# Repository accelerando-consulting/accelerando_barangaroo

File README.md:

# Accelerando Barangaroo

This is a simple breakout board for the eByte E73 module with nrf52832
microcontroller.  This board requires minimal parts, in fact it can
work with only the module and no other parts.

Add buttons and LEDs if you need, and there is space for two QWIIC
(I2C) sockets.

The board can be used with Arduino (Sandeep Mistry's nrf port with the
generic nrf52 target), or with Micro Python or Zephyr OS using the
included board definitions.

The circuit board files (for KiCad 5) are included.

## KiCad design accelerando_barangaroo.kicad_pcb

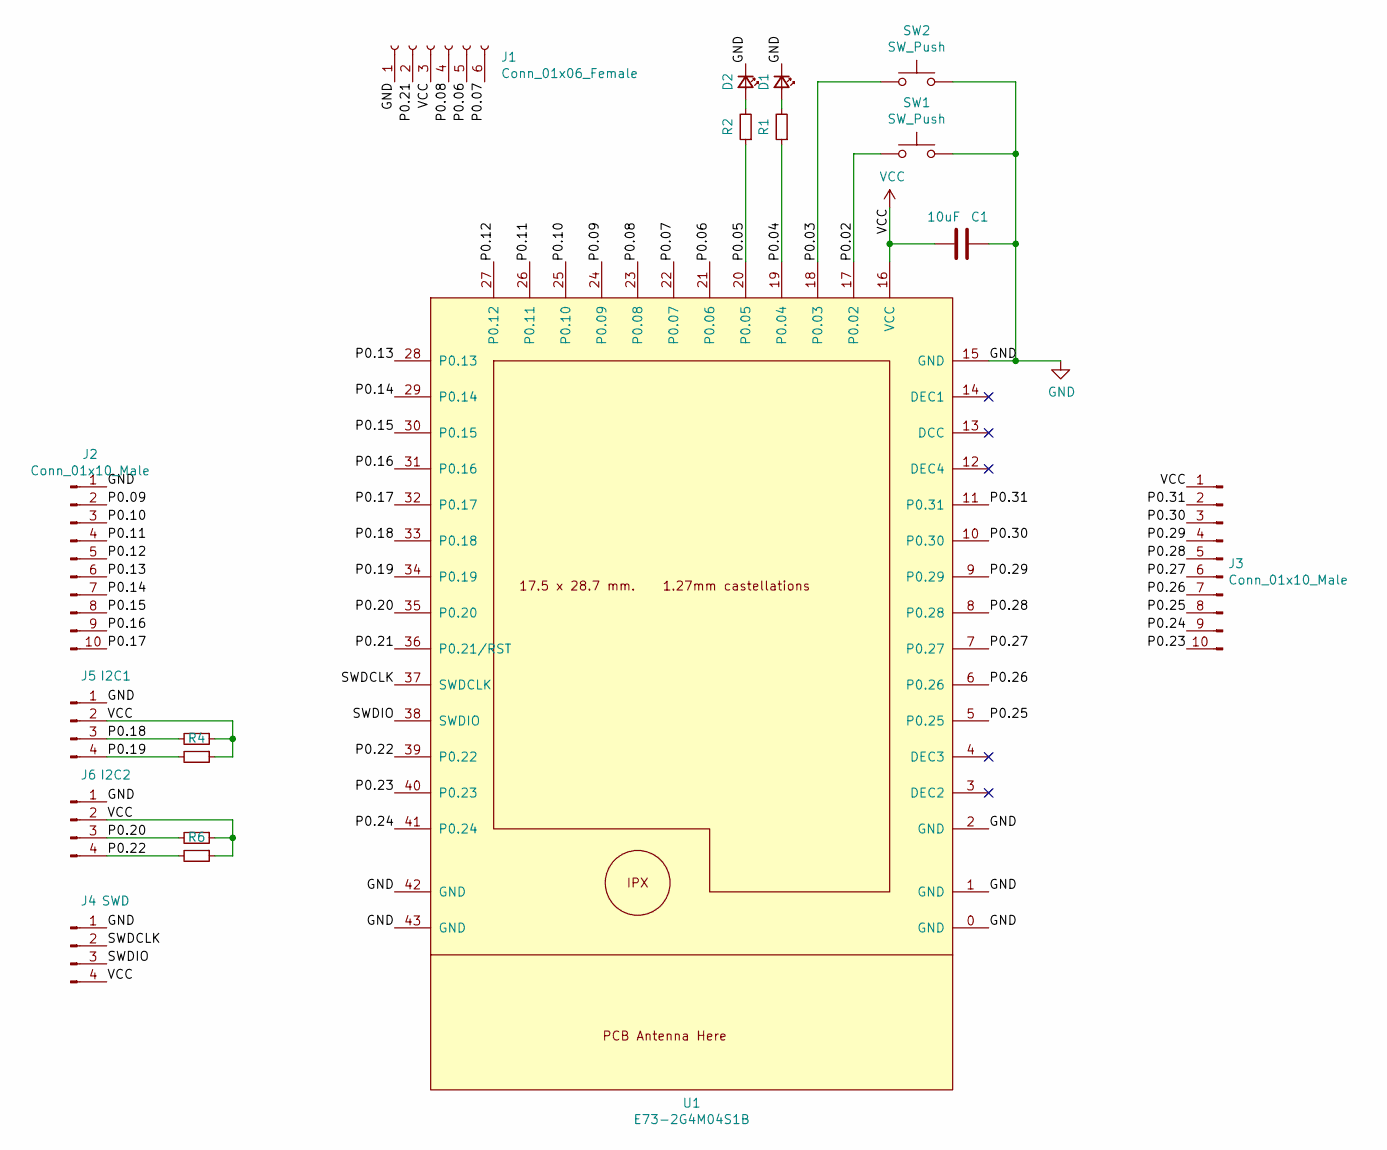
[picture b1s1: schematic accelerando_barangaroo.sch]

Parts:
C1: 10uF; C_0805_2012Metric
D1, D2: LED_Small; LED_0603_1608Metric
J1: Conn_01x06_Female; PinHeader_1x06_P2.54mm_Vertical
J2, J3: Conn_01x10_Male; PinHeader_1x10_P2.54mm_Vertical
J4: SWD; JST_PH_B4B-PH-K_1x04_P2.00mm_Vertical
J5: I2C1; JST_SH_BM04B-SRSS-TB_1x04-1MP_P1.00mm_Vertical
J6: I2C2; JST_SH_BM04B-SRSS-TB_1x04-1MP_P1.00mm_Vertical
R1, R2: R_Small; R_0603_1608Metric
R3, R4, R5, R6: R_Small; R_0402_1005Metric
SW1, SW2: SW_Push; SW_SPST_EVQPE1
U1: E73-2G4M04S1B

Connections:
/P0.02: SW1.1, U1.17 (P0.02)
/P0.03: SW2.1, U1.18 (P0.03)
/P0.04: R1.1, U1.19 (P0.04)
/P0.05: R2.1, U1.20 (P0.05)
/P0.06: J1.5, U1.21 (P0.06)
/P0.07: J1.6, U1.22 (P0.07)
/P0.08: J1.4, U1.23 (P0.08)
/P0.09: J2.2, U1.24 (P0.09)
/P0.10: J2.3, U1.25 (P0.10)
/P0.11: J2.4, U1.26 (P0.11)
/P0.12: J2.5, U1.27 (P0.12)
/P0.13: J2.6, U1.28 (P0.13)
/P0.14: J2.7, U1.29 (P0.14)
/P0.15: J2.8, U1.30 (P0.15)
/P0.16: J2.9, U1.31 (P0.16)
/P0.17: J2.10, U1.32 (P0.17)
/P0.18: J5.3, R3.2, U1.33 (P0.18)
/P0.19: J5.4, R4.2, U1.34 (P0.19)
/P0.20: J6.3, R5.2, U1.35 (P0.20)
/P0.21: J1.2, U1.36 (P0.21/RST)
/P0.22: J6.4, R6.2, U1.39 (P0.22)
/P0.23: J3.10, U1.40 (P0.23)
/P0.24: J3.9, U1.41 (P0.24)
/P0.25: J3.8, U1.5 (P0.25)
/P0.26: J3.7, U1.6 (P0.26)
/P0.27: J3.6, U1.7 (P0.27)
/P0.28: J3.5, U1.8 (P0.28)
/P0.29: J3.4, U1.9 (P0.29)
/P0.30: J3.3, U1.10 (P0.30)
/P0.31: J3.2, U1.11 (P0.31)
/SWDCLK: J4.2, U1.37 (SWDCLK)
/SWDIO: J4.3, U1.38 (SWDIO)
GND: C1.1, D1.1 (K), D2.1 (K), J1.1, J2.1, J4.1, J5.1, J6.1, SW1.2, SW2.2, U1.0 (GND), U1.1 (GND), U1.2 (GND), U1.15 (GND), U1.42 (GND), U1.43 (GND)
unnamed: D1.2 (A), R1.2
unnamed: D2.2 (A), R2.2
VCC: C1.2, J1.3, J3.1, J4.4, J5.2, J6.2, R3.1, R4.1, R5.1, R6.1, U1.16 (VCC)

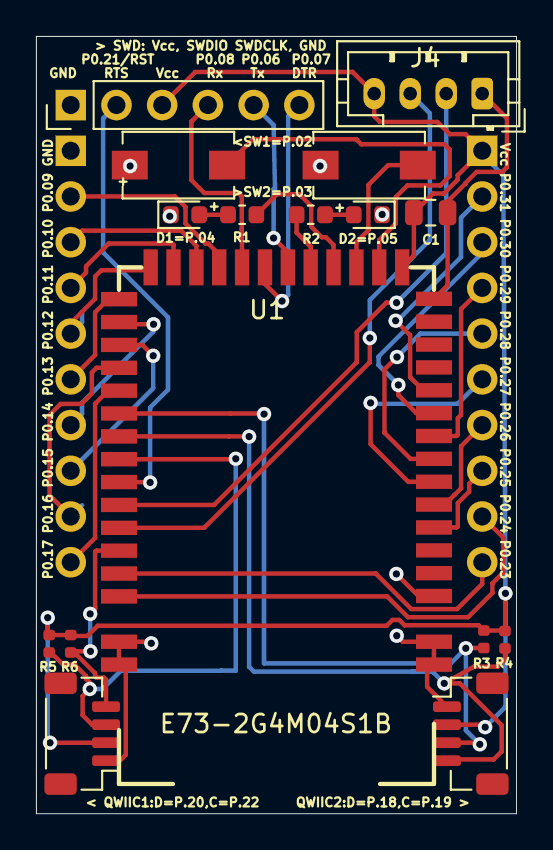
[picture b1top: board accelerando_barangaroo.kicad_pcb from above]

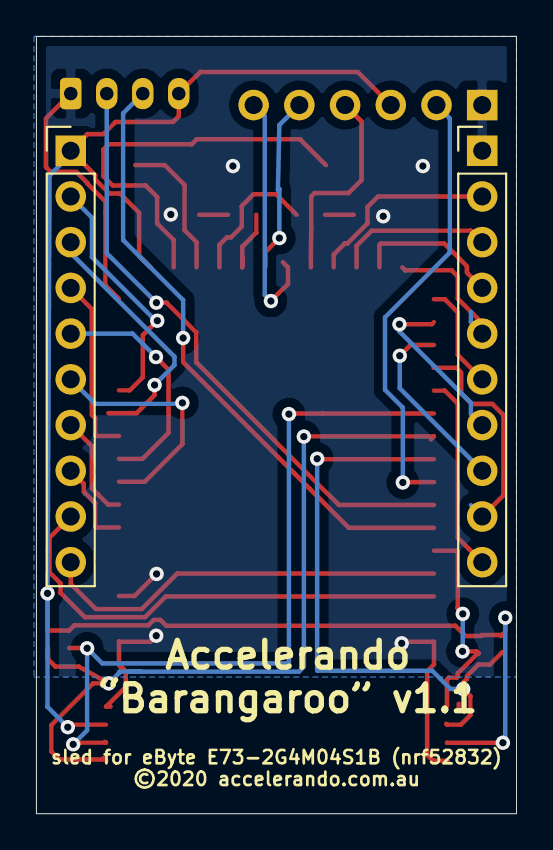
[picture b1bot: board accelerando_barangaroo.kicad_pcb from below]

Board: 2 copper layers, 26.7 x 43.2 mm, 18 parts (2 on the bottom side), 36 nets.

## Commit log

2021-04-19 Accelerando Barangaroo - Open Source nrf52832 breakout board
2021-04-19 Board definition for MicroPython
2021-04-19 Board definition for Zephyr
2021-04-19 Add README and LICENSE
2021-04-27 s/BSD/MIT/

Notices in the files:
accelerando_barangaroo.kicad_pcb:
©2020 accelerando.com.au
